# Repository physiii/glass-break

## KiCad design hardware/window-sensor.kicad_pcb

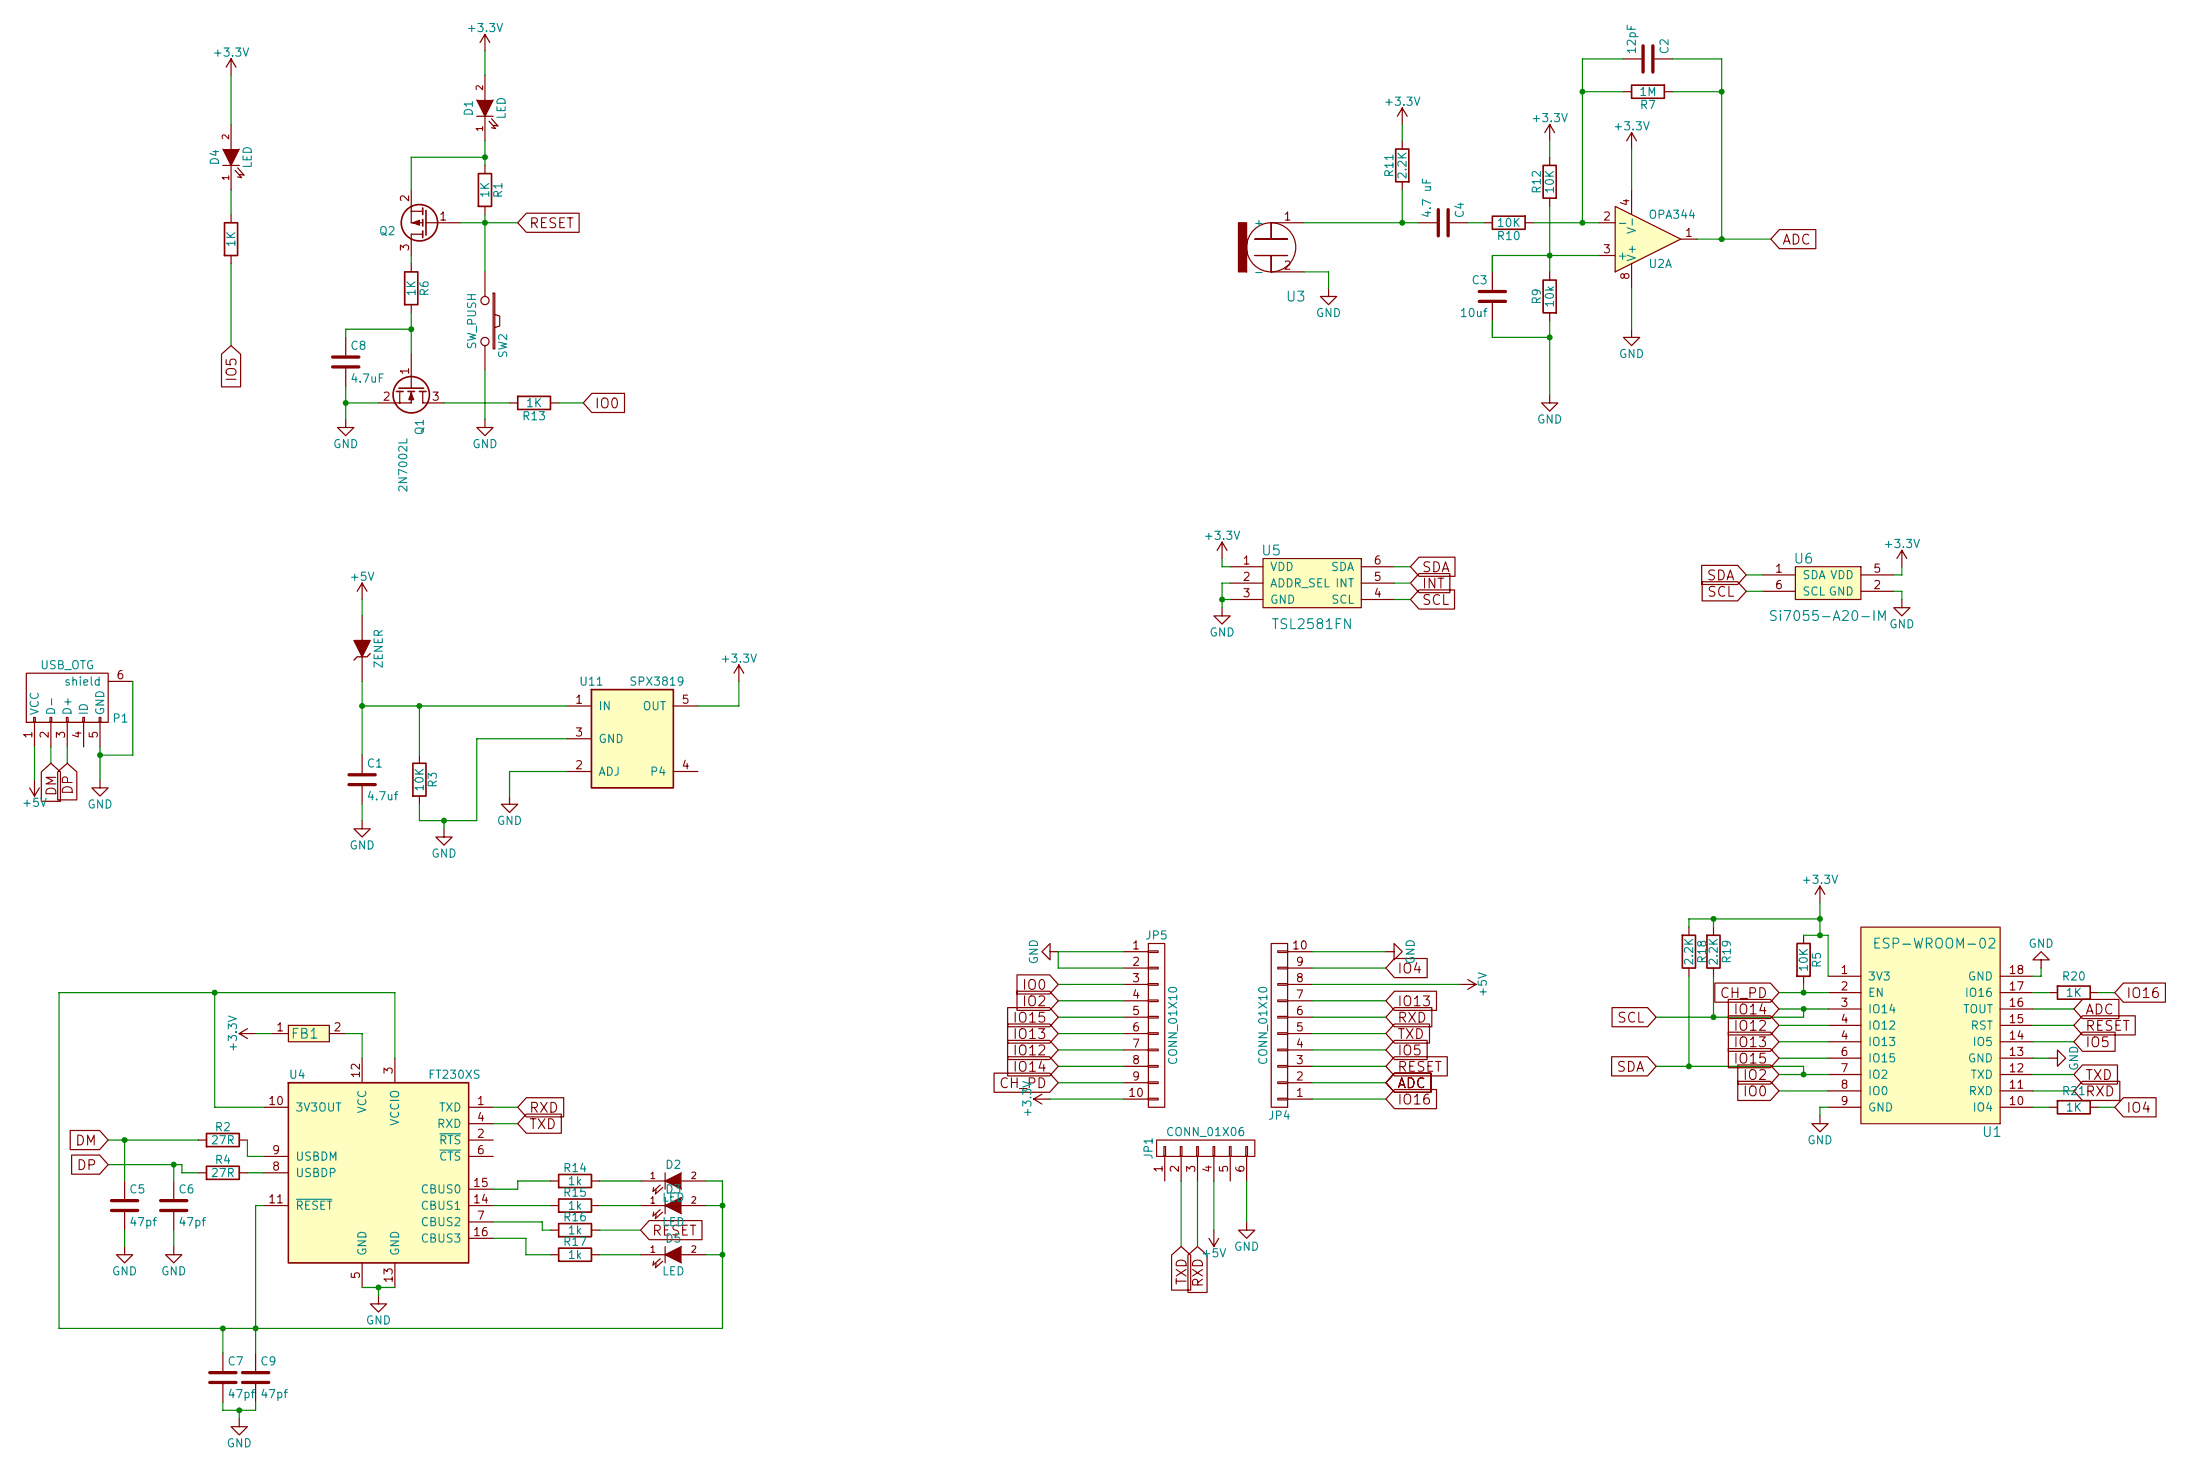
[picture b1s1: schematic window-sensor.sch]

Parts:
C1: 4.7uf; C_0805; Part Number VJ0805G475KXYTW1BC
C2: 12pF; R_0603; Part Number GRM0335C1H120GA01D
C3: 10uf; C_0805; Part Number VJ0805G106KXQTW1BC
C4: 4.7 uF; C_0805; Part Number C0603X5R1C472K030BA
C5, C6, C7, C9: 47pf; C_0603; Part Number VJ0603A470JXACW1BC
C8: 4.7uF; C_0805; Part Number VJ0805G475KXYTW1BC
D1, D2, D3, D4, D5: LED; LED_0805; Part Number LS Q976-NR-1
FB1: BLM18PG330SN1D; R_0603; Part Number BLM18PG330SN1D
JP1: CONN_01X06; Pin_Header_Straight_1x06
JP4, JP5: CONN_01X10; Pin_Header_Straight_1x10
MBR120-1: ZENER; SOD-123; Part Number MBR120VLSFT1G
P1: USB_OTG; USB_Micro-B; Part Number 10118194-0001LF
Q1: 2N7002L; SOT-23; Part Number 2N7002L
Q2: BSS84LT1G; SOT-23; Part Number BSS84LT1G
R1, R6, R8, R13, R20, R21: 1K; R_0603; Part Number ERJ-3EKF1001V
R2, R4: 27R; R_0603; Part Number ERJ-3GEYJ270V
R3, R5, R10, R12: 10K; R_0603; Part Number ERJ-3GEYJ103V
R7: 1M; R_0603; Part Number ERJ-3GEYJ105V
R9: 10k; R_0603; Part Number ERJ-3GEYJ103V
R11, R18, R19: 2.2K; R_0603; Part Number ERJ-3GEYJ222V
R14, R15, R16, R17: 1k; R_0603; Part Number ERJ-3EKF1001V
SW2: SW_PUSH; SW_SPST_KMR2; Part Number KMR211NG LFS
U1: ESP-WROOM-02; Part Number ESP-WROOM-02
U2: OPA344; SOIC-8_3.9x4.9mm_Pitch1.27mm; Part Number OPA344NA/3K
U3: CMC-5044PF-A; Electret; Part Number CMC-5044PF-A
U4: FT230XS; SSOP-16_3.9x4.9mm_Pitch0.635mm; Part Number FT230XS
U5: TSL2581FN; DFN-6-1EP_2x2mm_Pitch0.65mm; Part Number TSL2581FN
U6: Si7055-A20-IM; DFN-6-1EP_3x3mm_Pitch0.95mm; Part Number Si7055-A20-IM
U11: SPX3819; SOT-23-5; Part Number ERJ-3GEYJ103V

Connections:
+3V3: D1.2 (A), D4.2 (A), FB1.1, JP5.10, R5.1, R11.1, R12.1, R18.2, R19.2, U1.1 (3V3), U2.4 (V-), U5.1 (VDD), U6.5 (VDD), U11.5 (OUT)
+5V: JP1.4, JP4.8, MBR120-1.2 (A), P1.1 (VCC)
ADC: C2.1, JP4.2, R7.2, U1.16 (TOUT), U2.1
CH_PD: JP5.9, R5.2, U1.2 (EN)
DM: C5.1, P1.2 (D-), R2.2
DP: C6.1, P1.3 (D+), R4.2
GND: C1.2, C3.2, C5.2, C6.2, C7.2, C8.2, C9.2, JP1.6, JP4.10, JP5.1, JP5.2, P1.5 (GND), P1.6 (shield), Q1.2 (S), R3.2, R9.2, SW2.2, U1.9 (GND), U1.13 (GND), U1.18 (GND), U2.8 (V+), U3.2 (-), U4.5 (GND), U4.13 (GND), U5.2 (ADDR_SEL), U5.3 (GND), U6.2 (GND), U11.2 (ADJ), U11.3 (GND)
INT: U5.5 (INT)
IO0: JP5.3, R13.1, U1.8 (IO0)
IO2: JP5.4, R18.1, U1.7 (IO2), U5.6 (SDA), U6.1 (SDA)
IO4: JP4.9, R21.1
IO5: JP4.4, R8.2, U1.14 (IO5)
IO14: JP5.8, R19.1, U1.3 (IO14), U5.4 (SCL), U6.6 (SCL)
IO15: JP5.5, U1.6 (IO15)
IO16: JP4.1, R20.1
unnamed: C1.1, MBR120-1.1 (K), R3.1, U11.1 (IN)
unnamed: C2.2, R7.1, R10.2, U2.2 (-)
unnamed: C3.1, R9.1, R12.2, U2.3 (+)
unnamed: C4.1, R10.1
unnamed: C4.2, R11.2, U3.1 (+)
unnamed: C7.1, C9.1, D2.2 (A), D3.2 (A), D5.2 (A), U4.3 (VCCIO), U4.10 (3V3OUT), U4.11 (~RESET)
unnamed: C8.1, Q1.1 (G), R6.2
unnamed: D1.1 (K), Q2.2 (S), R1.1
unnamed: D2.1 (K), R14.1
unnamed: D3.1 (K), R15.1
unnamed: D4.1 (K), R8.1
unnamed: D5.1 (K), R17.1
unnamed: FB1.2, U4.12 (VCC)
unnamed: Q1.3 (D), R13.2
unnamed: Q2.3 (D), R6.1
unnamed: R2.1, U4.9 (USBDM)
unnamed: R4.1, U4.8 (USBDP)
unnamed: R14.2, U4.15 (CBUS0)
unnamed: R15.2, U4.14 (CBUS1)
unnamed: R16.2, U4.7 (CBUS2)
unnamed: R17.2, U4.16 (CBUS3)
unnamed: R20.2, U1.17 (IO16)
unnamed: R21.2, U1.10 (IO4)
RESET: JP4.3, Q2.1 (G), R1.2, R16.1, SW2.1, U1.15 (RST)
RXD: JP1.3, JP4.6, U1.11 (RXD), U4.1 (TXD)
TXD: JP1.2, JP4.5, U1.12 (TXD), U4.4 (RXD)

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
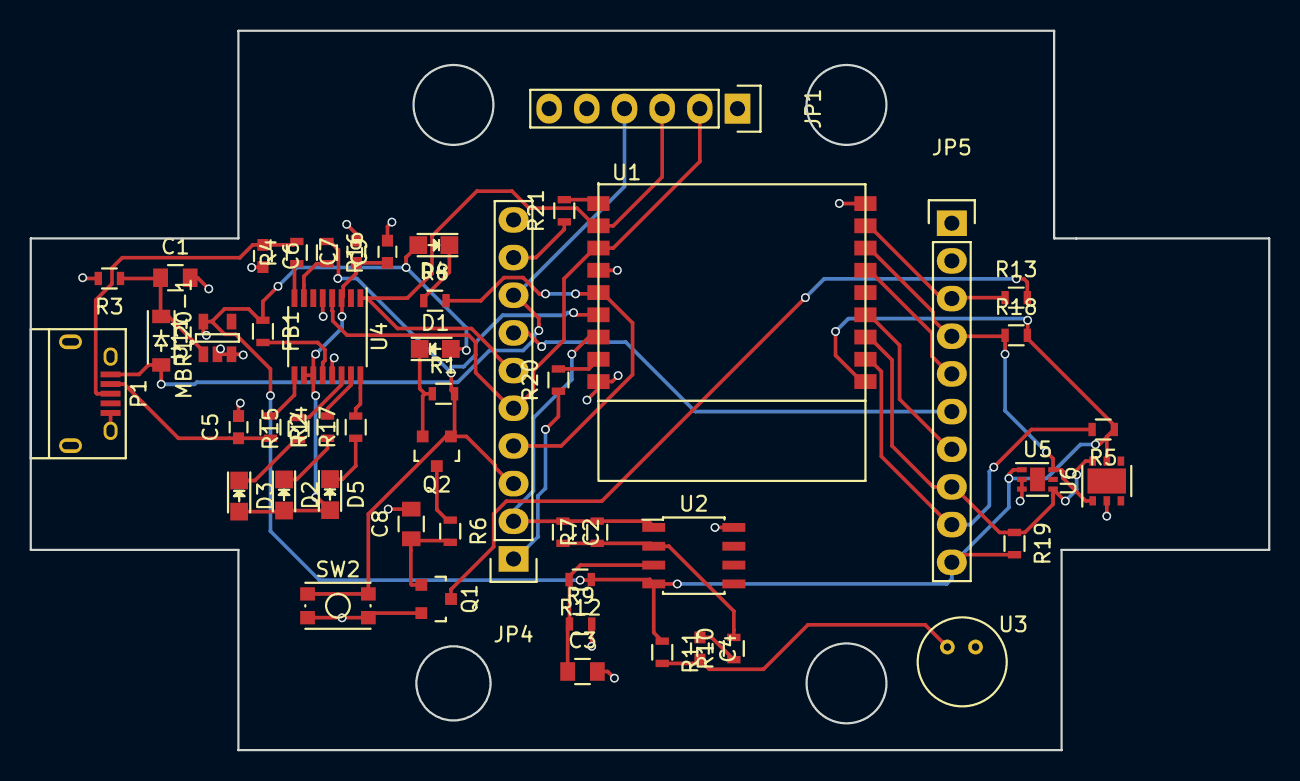
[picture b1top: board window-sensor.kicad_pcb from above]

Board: 2 copper layers, 83.5 x 48.5 mm, 51 parts (0 on the bottom side), 42 nets.

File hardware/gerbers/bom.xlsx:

Reference | Value | Footprint | Datasheet | Part Number
JP1 | CONN_01X06 | Pin_Headers:Pin_Header_Straight_1x06
JP4 | CONN_01X10 | Pin_Headers:Pin_Header_Straight_1x10
JP5 | CONN_01X10 | Pin_Headers:Pin_Header_Straight_1x10
U11 | SPX3819 | TO_SOT_Packages_SMD:SOT-23-5 | http://www.mouser.com/ds/2/146/SPX3819_DS_R200_082312-17072.pdf | ERJ-3GEYJ103V
R3 | 10K | Resistors_SMD:R_0603 | ERJ-3GEYJ103V | ERJ-3GEYJ103V
MBR120-1 | ZENER | Diodes_SMD:SOD-123 | MBR120VLSFT1G | MBR120VLSFT1G
C3 | 10uf | Capacitors_SMD:C_0805 | http://www.mouser.com/ds/2/400/lcc_commercial_general_en-837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 | VJ0805G106KXQTW1BC
C2 | 12pF | Resistors_SMD:R_0603 | GRM0335C1H120GA01D | GRM0335C1H120GA01D
C4 | 4.7 uF | Capacitors_SMD:C_0805 | C0603X5R1C472K030BA | C0603X5R1C472K030BA
R7 | 1M | Resistors_SMD:R_0603 | ERJ-3GEYJ105V | ERJ-3GEYJ105V
R9 | 10k | Resistors_SMD:R_0603 | ERJ-3GEYJ103V | ERJ-3GEYJ103V
R10 | 10K | Resistors_SMD:R_0603 | ERJ-3GEYJ103V | ERJ-3GEYJ103V
U2 | OPA344 | Housings_SOIC:SOIC-8_3.9x4.9mm_Pitch1.27mm | http://www.mouser.com/ds/2/609/OP275-879536.pdf | OPA344NA/3K
P1 | USB_OTG | Connect:USB_Micro-B | http://www.mouser.com/ds/2/123/690-005-299-143-262410.pdf | 10118194-0001LF
R1 | 1K | Resistors_SMD:R_0603 | ERJ-3EKF1001V | ERJ-3EKF1001V
SW2 | SW_PUSH | Buttons_Switches_SMD:SW_SPST_KMR2 | http://www.mouser.com/ds/2/60/KMR2_9aug12-25127.pdf | KMR211NG LFS
R8 | 1K | Resistors_SMD:R_0603 | ERJ-3EKF1001V | ERJ-3EKF1001V
D4 | LED | LEDs:LED_0805 | LS Q976-NR-1 | LS Q976-NR-1
R12 | 10K | Resistors_SMD:R_0603 | ERJ-3GEYJ103V | ERJ-3GEYJ103V
R11 | 2.2K | Resistors_SMD:R_0603 | ERJ-3GEYJ222V | ERJ-3GEYJ222V
U3 | CMC-5044PF-A | esp12e:Electret | http://www.mouser.com/ds/2/670/cmc-5044pf-a-515902.pdf | CMC-5044PF-A
U1 | ESP-WROOM-02 | garage-opener:ESP-WROOM-02 | http://espressif.com/en/products/hardware/esp-wroom-02/resources | ESP-WROOM-02
R5 | 10K | Resistors_SMD:R_0603 | ERJ-3GEYJ103V | ERJ-3GEYJ103V
Q2 | BSS84LT1G | TO_SOT_Packages_SMD:SOT-23 | http://www.mouser.com/ds/2/308/BSS84LT1-D-105913.pdf | BSS84LT1G
R6 | 1K | Resistors_SMD:R_0603 | ERJ-3EKF1001V | ERJ-3EKF1001V
Q1 | 2N7002L | TO_SOT_Packages_SMD:SOT-23 | http://www.mouser.com/ds/2/308/2N7002L-D-105484.pdf | 2N7002L
D1 | LED | LEDs:LED_0805 | LS Q976-NR-1 | LS Q976-NR-1
C8 | 4.7uF | Capacitors_SMD:C_0805 | VJ0805G475KXYTW1BC | VJ0805G475KXYTW1BC
R13 | 1K | Resistors_SMD:R_0603 | ERJ-3EKF1001V | ERJ-3EKF1001V
FB1 | BLM18PG330SN1D | Resistors_SMD:R_0603 | http://www.murata.com/~/media/webrenewal/support/library/cat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 | BLM18PG330SN1D
U4 | FT230XS | Housings_SSOP:SSOP-16_3.9x4.9mm_Pitch0.635mm | http://www.mouser.com/ds/2/163/DS_FT230X-5395.pdf | FT230XS
R14 | 1k | Resistors_SMD:R_0603 | ERJ-3EKF1001V | ERJ-3EKF1001V
R15 | 1k | Resistors_SMD:R_0603 | ERJ-3EKF1001V | ERJ-3EKF1001V
R16 | 1k | Resistors_SMD:R_0603 | ERJ-3EKF1001V | ERJ-3EKF1001V
R17 | 1k | Resistors_SMD:R_0603 | ERJ-3EKF1001V | ERJ-3EKF1001V
D2 | LED | LEDs:LED_0805 | LS Q976-NR-1 | LS Q976-NR-1
D3 | LED | LEDs:LED_0805 | LS Q976-NR-1 | LS Q976-NR-1
D5 | LED | LEDs:LED_0805 | LS Q976-NR-1 | LS Q976-NR-1
R2 | 27R | Resistors_SMD:R_0603 | ERJ-3GEYJ270V | ERJ-3GEYJ270V
R4 | 27R | Resistors_SMD:R_0603 | ERJ-3GEYJ270V | ERJ-3GEYJ270V
C6 | 47pf | Capacitors_SMD:C_0603 | VJ0603A470JXACW1BC | VJ0603A470JXACW1BC
C5 | 47pf | Capacitors_SMD:C_0603 | VJ0603A470JXACW1BC | VJ0603A470JXACW1BC
U6 | Si7055-A20-IM | Housings_DFN_QFN:DFN-6-1EP_3x3mm_Pitch0.95mm | http://www.mouser.com/ds/2/368/Si7050-1-3-4-5-A20-907443.pdf | Si7055-A20-IM
R19 | 2.2K | Resistors_SMD:R_0603 | ERJ-3GEYJ222V | ERJ-3GEYJ222V
R18 | 2.2K | Resistors_SMD:R_0603 | ERJ-3GEYJ222V | ERJ-3GEYJ222V
U5 | TSL2581FN | Housings_DFN_QFN:DFN-6-1EP_2x2mm_Pitch0.65mm | http://www.mouser.com/ds/2/588/TSL2581TSL2583-519228.pdf | TSL2581FN
R20 | 1K | Resistors_SMD:R_0603 | ERJ-3EKF1001V | ERJ-3EKF1001V
R21 | 1K | Resistors_SMD:R_0603 | ERJ-3EKF1001V | ERJ-3EKF1001V
C1 | 4.7uf | Capacitors_SMD:C_0805 | VJ0805G475KXYTW1BC | VJ0805G475KXYTW1BC
C9 | 47pf | Capacitors_SMD:C_0603 | VJ0603A470JXACW1BC | VJ0603A470JXACW1BC
C7 | 47pf | Capacitors_SMD:C_0603 | VJ0603A470JXACW1BC | VJ0603A470JXACW1BC

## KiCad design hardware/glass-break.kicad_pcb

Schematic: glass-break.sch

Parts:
C1: 1uf; C_0805
C2: 12pF; C_0805
C3: 10uF; C_0805
C4: 4.7 uF; C_0805
D1, D2: D; LED_0805
D3, D4: LED; LED_0805
JP1: CONN_01X06; Pin_Header_Straight_1x06
JP4, JP5: CONN_01X10; Pin_Header_Straight_1x10
MBR120-1, MBR120-2: ZENER; SOD-123
P1: USB_OTG; USB_Micro-B
R1, R3, R4, R5, R6, R10, R12: 10K; R_0805
R2, R8: 1K; R_0805
R7: 1M; R_0805
R9: 10k; R_0805
R11: 2.2K; R_0805
SW1, SW2, SW3: SW_PUSH; SW_SPST_KMR2
U1: ESP-WROOM-02
U2: OP275; SOIC-8_3.9x4.9mm_Pitch1.27mm
U3: electret_microphone; Electret
U11: SPX3819; SOT-23-5(MOD)

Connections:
1O0: JP5.3
+3V3: D3.2 (A), D4.2 (A), JP5.10, R1.1, R4.1, R5.1, R11.1, R12.1, U1.18 (GND), U2.4 (V-), U11.5 (OUT)
+5V: JP1.4, JP4.8, MBR120-1.2 (A), P1.1 (VCC)
+BATT: JP4.9, MBR120-2.2 (A)
ADC: C2.1, JP4.2, R7.2, U1.3 (IO14), U2.1
CH_PD: JP5.9, R5.2, U1.17 (IO16)
GND: C1.2, C3.2, JP1.6, JP4.10, JP5.1, JP5.2, P1.5 (GND), P1.6 (shield), R6.2, R9.2, SW1.2, SW2.2, SW3.2, U1.1 (3V3), U1.6 (IO15), U1.10 (IO4), U2.8 (V+), U3.2 (-), U11.2 (ADJ)
I02: JP5.4
I015: JP5.5
IO0: R2.2, SW1.1, U1.11 (RXD)
IO2: R4.2, U1.12 (TXD)
IO4: SW3.1, U1.9 (GND)
IO12: JP5.7, U1.15 (RST)
IO13: JP4.7, JP5.6, U1.14 (IO5)
IO14: JP5.8, U1.16 (TOUT)
IO15: R6.1, U1.13 (GND)
IO16: JP4.3, U1.2 (EN)
unnamed: C1.1, MBR120-1.1 (K), MBR120-2.1 (K), R3.1, U11.1 (IN)
unnamed: C2.2, R7.1, R10.2, U2.2 (-)
unnamed: C3.1, R9.1, R12.2, U2.3 (+)
unnamed: C4.1, R10.1
unnamed: C4.2, R11.2, U3.1 (+)
unnamed: D3.1 (K), R2.1
unnamed: D4.1 (K), R8.1
unnamed: R3.2, U11.3 (GND)
RESET_3V3: D1.1, JP4.1, R1.2, SW2.1
RXD: D2.2, U1.8 (IO0)
RXD_5V: D2.1, JP1.3, JP4.6
TXD: JP1.2, JP4.5, U1.7 (IO2)

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
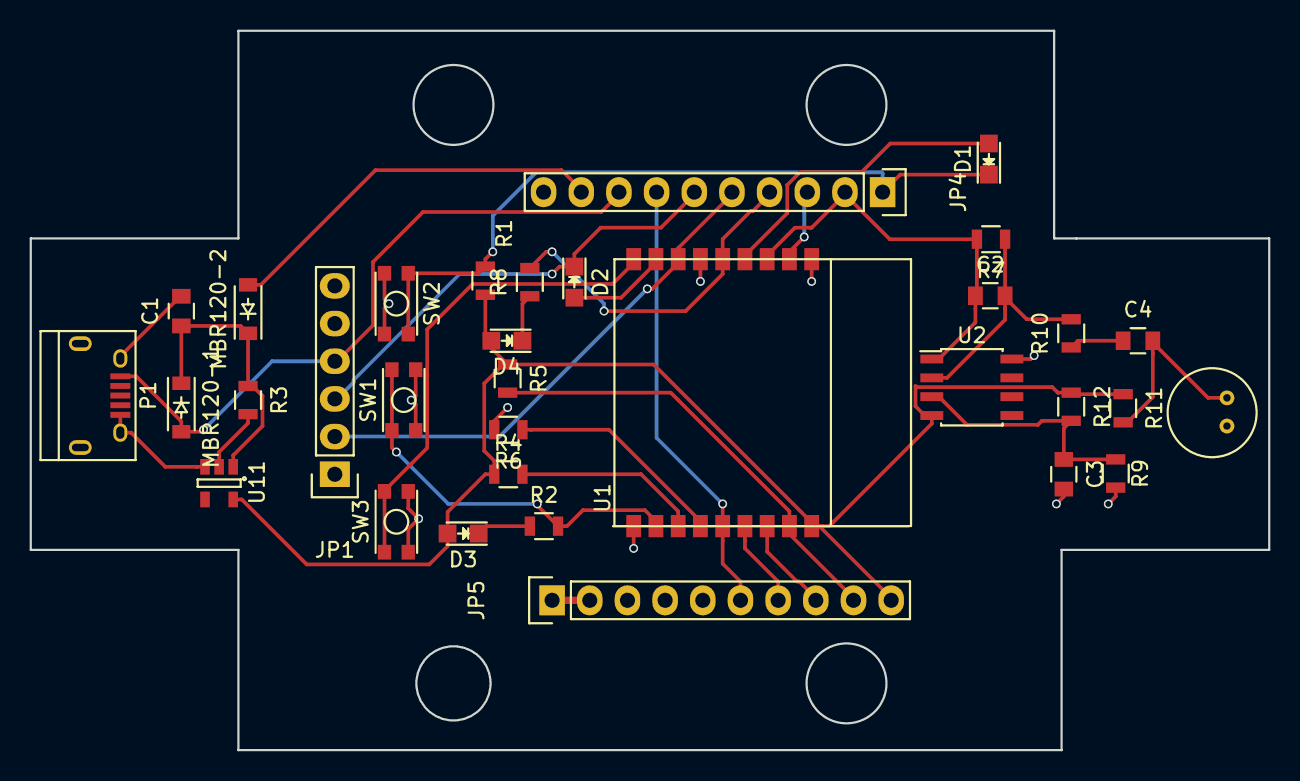
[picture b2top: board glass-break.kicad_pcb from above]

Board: 2 copper layers, 83.5 x 48.5 mm, 33 parts (0 on the bottom side), 28 nets.

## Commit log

2015-12-28 added schematic components
2016-01-08 schematic update
2016-02-09 wifi setup
2016-02-11 websockets added
2016-02-12 ws update
2016-02-12 websocket update
2016-02-12 updated websockets
2016-02-12 websockets update
2016-02-19 sch update
2016-03-05 layout update
2016-03-05 added dimensions update
2016-03-07 datasheetupdate
2016-03-08 footprint update
2016-03-08 pcd update
2016-03-09 PCB attempt
2016-03-10 pcb trial2
2016-03-10 pcb 3
